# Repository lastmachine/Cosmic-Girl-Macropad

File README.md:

# Cosmic-Girl-Macropad
A personal cosmic-themed XIAO-RP2040-powered macropad for games, video editing, or anything you'd like to customize. It features 9 MX-style switches, 1 EC11 rotary encoder, and a 128x32 OLED screen.

Having 9 keys makes it perfect for media editing and streaming; those are the main usages I want to give it. Of course, this macropad would work for anything else that allows custom binds. KMK firmware written in Python, is open to modifications 

It is called "Cosmic Girl" because I really like the song of the same name created by the band "Jamiroquai," and also space aesthetics.

Made using KiCad, Fusion 360, and Visual Studio Code. For Hack Club Blueprint.

## Render & Snapshot - Fusion 360

---
## PCB & Schematic - KiCad 

---
## 3D

---
## Bill of Materials

| Part | Quantity | Details |
|------|----------|-------|
| Seeed XIAO RP2040 | 1 | Unsoldered |
| 1N4148 Diode | 10 | Through-hole |
| MX-Style Switch | 9 | |
| EC11 Rotary Encoder | 1 | D-Shaft |
| 0.91" OLED Display | 1 | I2C, 128x32 |
| DSA Keycap (white blank) | 9 | |
| SK6812 MINI-E LED | 9 | |
| M3x16mm Screw | 4 | |
| M3x5x4mm Heatset Insert | 4 | |
| Custom PCB | 1 | 2-layer, 98x98mm|

---
## Attribution
Rotary encoder knob model adapted from [EC11 Encoder Knob](https://www.printables.com/model/1000044-ec11-encoder-knob) by Kea Workshop, licensed under GNU GPL v2.0

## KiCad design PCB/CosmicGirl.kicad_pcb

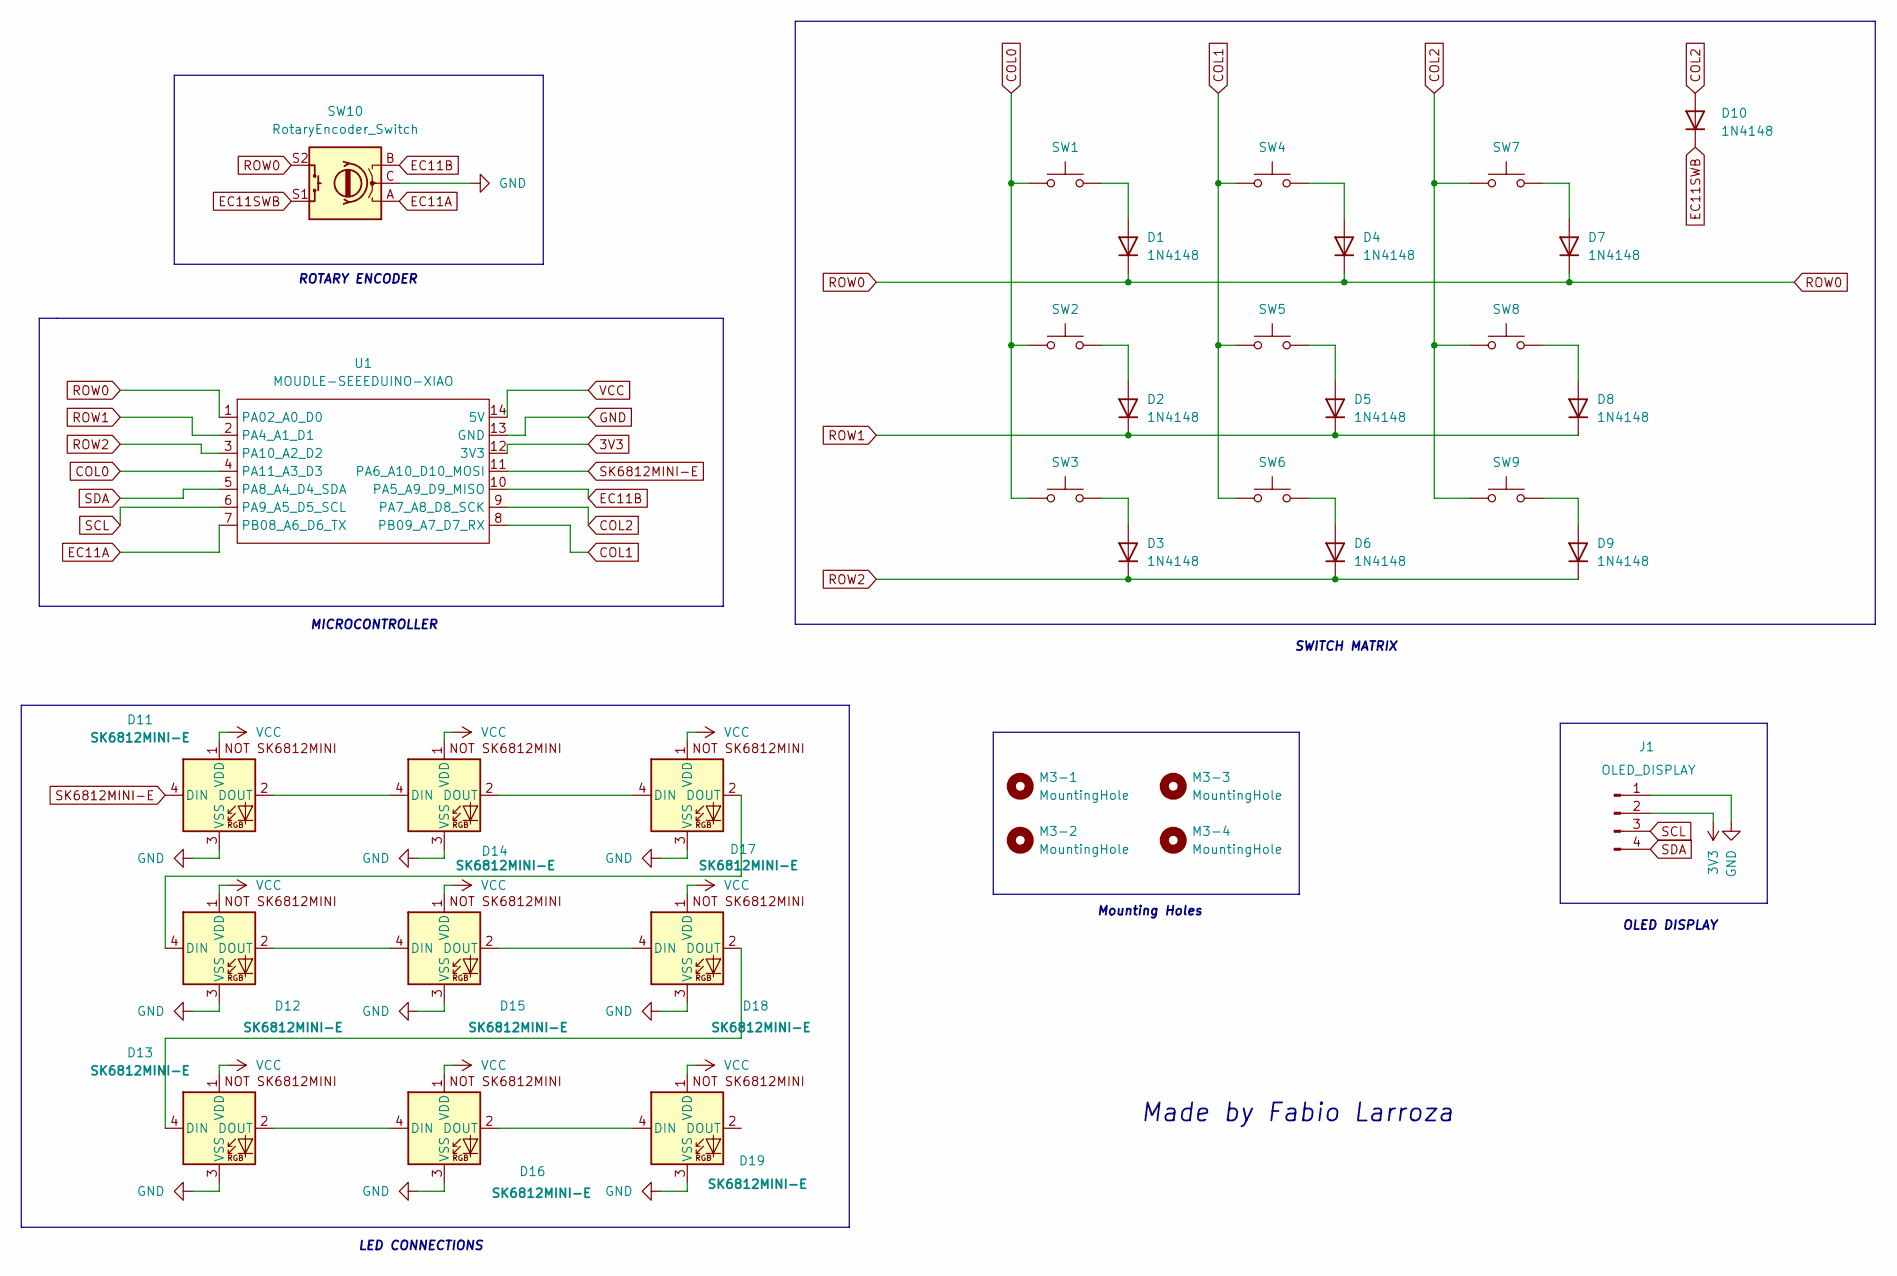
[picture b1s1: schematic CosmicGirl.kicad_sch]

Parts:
D1, D2, D3, D4, D5, D6, D7, D8, D9, D10: 1N4148; D_DO-35_SOD27_P7.62mm_Horizontal
D11, D12, D13, D14, D15, D16, D17, D18, D19: SK6812MINI-E; SK6812MINI-E_fixed
J1: OLED_DISPLAY; SSD1306-0.91-OLED-4pin-128x32
M3-1, M3-2, M3-3, M3-4: MountingHole; MountingHole_3.2mm_M3
SW1, SW2, SW3, SW4, SW5, SW6, SW7, SW8, SW9: SW_Push; SW_Cherry_MX_1.00u_PCB
SW10: RotaryEncoder_Switch; RotaryEncoder_Alps_EC11E-Switch_Vertical_H20mm
U1: MOUDLE-SEEEDUINO-XIAO; XIAO-Generic-Hybrid-14P-2.54-21X17.8MM

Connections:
3V3: J1.2, U1.12 (3V3)
COL0: SW1.1, SW2.1, SW3.1, U1.4 (PA11_A3_D3)
COL1: SW4.1, SW5.1, SW6.1, U1.8 (PB09_A7_D7_RX)
COL2: D10.2 (A), SW7.1, SW8.1, SW9.1, U1.9 (PA7_A8_D8_SCK)
EC11A: SW10.A, U1.7 (PB08_A6_D6_TX)
EC11B: SW10.B, U1.10 (PA5_A9_D9_MISO)
EC11SWB: D10.1 (K), SW10.S1
GND: D11.3 (VSS), D12.3 (VSS), D13.3 (VSS), D14.3 (VSS), D15.3 (VSS), D16.3 (VSS), D17.3 (VSS), D18.3 (VSS), D19.3 (VSS), J1.1, SW10.C, U1.13 (GND)
unnamed: D1.2 (A), SW1.2
unnamed: D2.2 (A), SW2.2
unnamed: D3.2 (A), SW3.2
unnamed: D4.2 (A), SW4.2
unnamed: D5.2 (A), SW5.2
unnamed: D6.2 (A), SW6.2
unnamed: D7.2 (A), SW7.2
unnamed: D8.2 (A), SW8.2
unnamed: D9.2 (A), SW9.2
unnamed: D11.2 (DOUT), D14.4 (DIN)
unnamed: D12.4 (DIN), D17.2 (DOUT)
unnamed: D12.2 (DOUT), D15.4 (DIN)
unnamed: D13.4 (DIN), D18.2 (DOUT)
unnamed: D13.2 (DOUT), D16.4 (DIN)
unnamed: D14.2 (DOUT), D17.4 (DIN)
unnamed: D15.2 (DOUT), D18.4 (DIN)
unnamed: D16.2 (DOUT), D19.4 (DIN)
ROW0: D1.1 (K), D4.1 (K), D7.1 (K), SW10.S2, U1.1 (PA02_A0_D0)
ROW1: D2.1 (K), D5.1 (K), D8.1 (K), U1.2 (PA4_A1_D1)
ROW2: D3.1 (K), D6.1 (K), D9.1 (K), U1.3 (PA10_A2_D2)
SCL: J1.3, U1.6 (PA9_A5_D5_SCL)
SDA: J1.4, U1.5 (PA8_A4_D4_SDA)
SK6812MINI-E: D11.4 (DIN), U1.11 (PA6_A10_D10_MOSI)
VCC: D11.1 (VDD), D12.1 (VDD), D13.1 (VDD), D14.1 (VDD), D15.1 (VDD), D16.1 (VDD), D17.1 (VDD), D18.1 (VDD), D19.1 (VDD), U1.14 (5V)

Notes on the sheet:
OLED DISPLAY
ROTARY ENCODER
LED CONNECTIONS
MICROCONTROLLER
SWITCH MATRIX
Made by Fabio Larroza
Mounting Holes

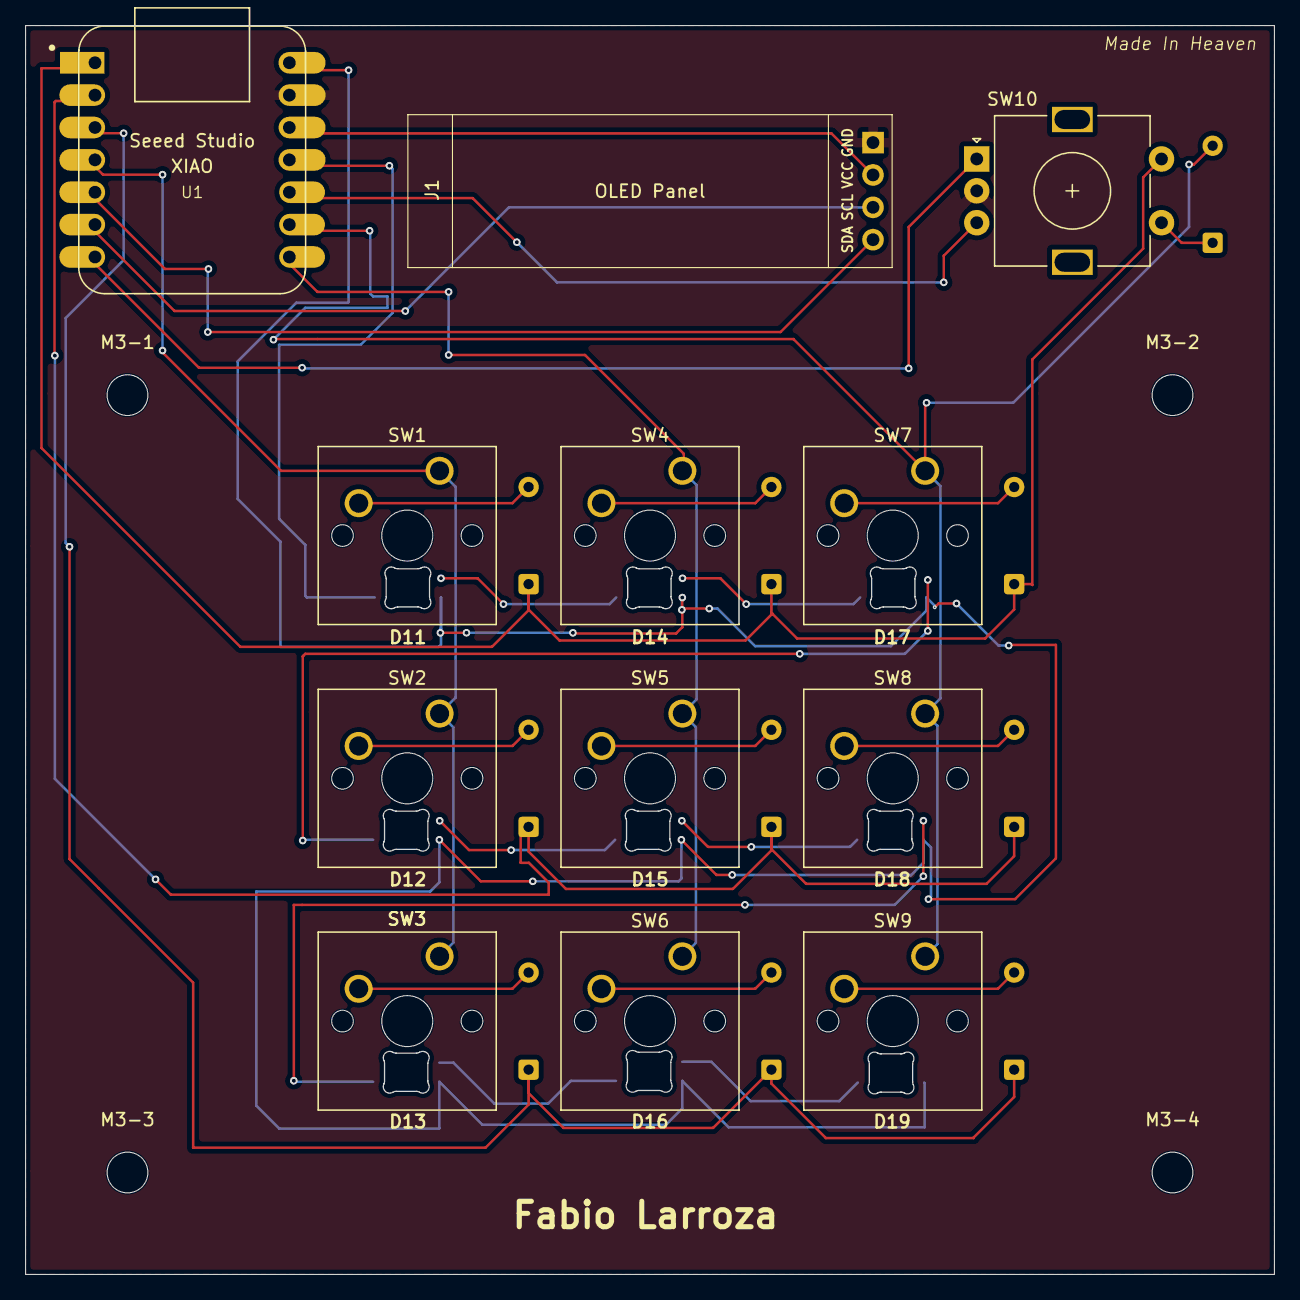
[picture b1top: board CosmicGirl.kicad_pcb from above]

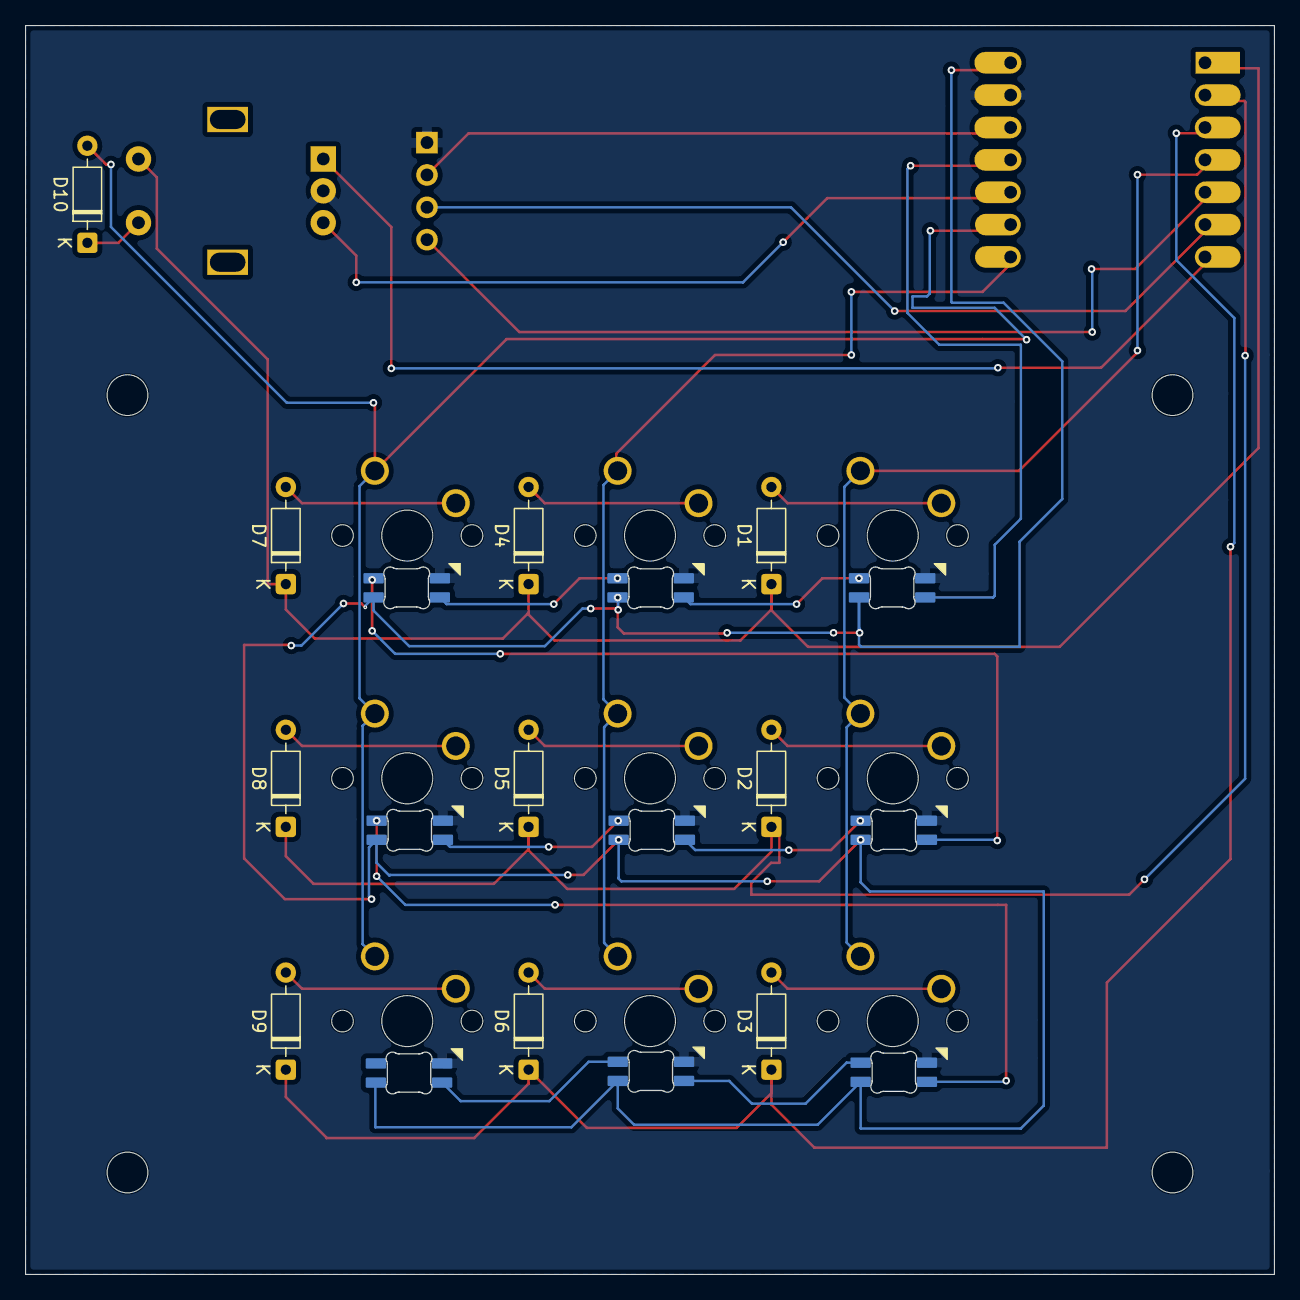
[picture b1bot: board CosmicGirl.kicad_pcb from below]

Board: 2 copper layers, 97.9 x 97.9 mm, 35 parts (10 on the bottom side), 32 nets.

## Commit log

2026-03-31 First upload
    Uploading first project files
2026-03-31 More uploads
2026-03-31 Revise description for Cosmic-Girl-Macropad
    Updated wording for clarity in the README.
2026-03-31 Fix typo in project description
